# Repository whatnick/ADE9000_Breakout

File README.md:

# ADE9000 Breakout Board

Breadboard-compatible breakout for the Analog Devices [ADE9000](https://www.analog.com/en/products/ade9000.html) — a high-performance, multiphase energy and power quality monitoring IC.

The board follows the **test circuit from Figure 55 of the ADE9000 datasheet** (Rev. B, p. 28): all onboard passives (decoupling, RC anti-aliasing filters, crystal load caps, reset RC) are populated, power plus the analog channels are broken out to 0.1" headers, and the remaining digital signals are exposed on test pads to keep the board compact.

## 3D renders

These views are rendered from the populated KiCad assembly using the
project-local STEP models.

| Top isometric | Bottom isometric |
|---------------|------------------|
|  |  |

---

## Features

- **ADE9000** in 40-lead LFCSP (CP-40-7) package
- 3.3 V single-supply operation
- Onboard **24.576 MHz crystal** with 16 pF load caps (CLKIN/CLKOUT)
- Onboard **RC anti-aliasing filters** on all 7 analog input pairs (1 kΩ + 22 nF)
- Onboard **reset RC** (10 kΩ pull-up + 1 µF)
- Onboard **decoupling** on VDD, AVDDOUT, DVDDOUT, and REF per datasheet
- **CF2 activity LED** with 1 kΩ current-limit resistor
- **Power plus analog inputs** broken out to 0.1" headers
- **SPI, CF, IRQ, CLK, and RESET** exposed on test pads
- ATM90E36-style three-pad solder bridges for manual PM0/PM1 mode selection

---

## Pin Headers

### J1 — Power

| Pin | Signal | ADE9000 Pin | Description |
|-----|--------|-------------|-------------|
| 1 | 3.3V | — | Power in |
| 2 | GND | — | Ground |

### J2 — Current Inputs (left side, top)

| Pin | Signal | ADE9000 Pin | Description |
|-----|--------|-------------|-------------|
| 1 | IAP | 7 | Phase A current, positive |
| 2 | IAN | 8 | Phase A current, negative |
| 3 | IBP | 9 | Phase B current, positive |
| 4 | IBN | 10 | Phase B current, negative |
| 5 | ICP | 11 | Phase C current, positive |
| 6 | ICN | 12 | Phase C current, negative |
| 7 | INP | 13 | Neutral current, positive |
| 8 | INN | 14 | Neutral current, negative |

> Each input pair has a 1 kΩ series resistor and 22 nF cap to GND already fitted on board. Max differential input ±1 V / PGA gain.

### J3 — Voltage Inputs (left side, bottom)

| Pin | Signal | ADE9000 Pin | Description |
|-----|--------|-------------|-------------|
| 1 | VAP | 20 | Phase A voltage, positive |
| 2 | VAN | 19 | Phase A voltage, negative |
| 3 | VBP | 22 | Phase B voltage, positive |
| 4 | VBN | 21 | Phase B voltage, negative |
| 5 | VCP | 24 | Phase C voltage, positive |
| 6 | VCN | 23 | Phase C voltage, negative |

> Each input pair has the same 1 kΩ + 22 nF RC filter as the current inputs.

### Test Pads — Digital I/O

| Pad | Signal | ADE9000 Pin | Description |
|-----|--------|-------------|-------------|
| TP1 | SS | 40 | SPI slave select (active low) |
| TP2 | MOSI | 39 | SPI data in |
| TP3 | MISO | 38 | SPI data out |
| TP4 | SCLK | 37 | SPI clock (up to 20 MHz) |
| TP5 | IRQ0 | 31 | Interrupt output 0 (active low) |
| TP6 | IRQ1 | 32 | Interrupt output 1 (active low) |
| TP7 | CF1 | 33 | Calibration frequency output 1 |
| TP8 | CF2 | 34 | Calibration frequency output 2 / LED drive |
| TP9 | CF3_ZX | 35 | Zero-cross / CF3 output |
| TP10 | CF4_DREADY | 36 | Data-ready / event / CF4 output |
| TP11 | RESET | 6 | Reset (active low, RC-held high) |

---

## Power

- Supply **3.3 V** into the J1 3.3V pin (or the dedicated 3V3 pad).
- Current draw: ~15–17 mA in normal mode (PSM0).
- Onboard decoupling (per datasheet §Test Circuit):
  - **VDD** (pin 27): 10 µF + 0.1 µF ceramic to GND
  - **AVDDOUT** (pin 25): 4.7 µF + 0.1 µF ceramic to GND — **do not drive externally**
  - **DVDDOUT** (pin 3): 4.7 µF + 0.1 µF ceramic to GND — **do not drive externally**
  - **REF** (pin 16): 4.7 µF + 0.1 µF ceramic to REFGND (internal 1.25 V reference)

### PM0/PM1 mode bridges

`JP1` controls PM0 and `JP2` controls PM1. Each open three-pad jumper is marked
`1 PMx 0`: bridge the center pad to `1` for `+3V3`, or to `0` for `GND`.

| JP2 / PM1 | JP1 / PM0 | Selection |
|------------|-----------|-----------|
| 0 | 0 | Normal operation |
| 0 | 1 | PM1:PM0 = `01` |
| 1 | 0 | PM1:PM0 = `10` |
| 1 | 1 | PM1:PM0 = `11` |

Bridge exactly one side of each jumper before powering the board. Never bridge
both sides, and do not leave a mode pin floating. Production boards intended
for normal operation should have the `0` side bridged on both JP1 and JP2.

---

## Clock

A 24.576 MHz crystal is fitted between CLKIN (pin 29) and CLKOUT (pin 30) with 16 pF load capacitors to GND. This matches the ADE9000's required ±30 ppm clock.

To use an external clock instead, remove the crystal, leave the load caps unpopulated, and drive CLKIN directly (3.3 V logic, 24.330–24.822 MHz, 45:55–55:45 duty cycle).

---

## SPI Interface

The ADE9000 uses **SPI mode 0** (CPOL=0, CPHA=0), MSB first, up to **20 MHz**.

| Signal | Direction (from MCU) | Notes |
|--------|---------------------|-------|
| SCLK | Output | Max 20 MHz |
| MOSI | Output | 16-bit or 32-bit transfers |
| MISO | Input | |
| SS | Output | Assert low before each transfer |

All SPI pins are 3.3 V logic. Use a level shifter if connecting to a 5 V MCU.

---

## Analog Input Signal Conditioning

The onboard RC filter on each analog input pin:

```
Signal ──[ 1 kΩ ]──┬── IxP / VxP (ADE9000 pin)
                   │
                 [22 nF]
                   │
                  GND
```

This provides a first-order anti-aliasing LPF with fc ≈ 7.2 kHz, matching the ADC's −3 dB bandwidth. For CT or Rogowski coil inputs, drive the differential pair through an additional burden resistor or signal conditioning stage before these onboard filters.

---

## BOM Summary

Source purchasing fields live on the schematic symbols as `Manufacturer`, `MPN`, `DigiKey`, `Mouser`, and `Description` properties. Regenerate the grouped purchasing BOM with:

```powershell
& "C:\Program Files\KiCad\10.0\bin\python.exe" .\scripts\apply_bom_fields.py
& "C:\Program Files\KiCad\10.0\bin\python.exe" .\scripts\export_bom.py --html .\bom\ADE9000_Breakout_BOM.html
```

Generated outputs are available as [`bom/ADE9000_Breakout_BOM.csv`](bom/ADE9000_Breakout_BOM.csv), [`bom/ADE9000_Breakout_BOM.xlsx`](bom/ADE9000_Breakout_BOM.xlsx), and [`bom/ADE9000_Breakout_BOM.html`](bom/ADE9000_Breakout_BOM.html). The DigiKey and Mouser fields use distributor search URLs for the selected manufacturer MPNs so stock and packaging can be checked at order time.

| Ref | Value | Package | Notes |
|-----|-------|---------|-------|
| U1 | ADE9000 | CP-40-7 LFCSP | Main IC |
| Y1 | 24.576 MHz | 3225 (3.2×2.5 mm) | ±30 ppm |
| C_CLKIN, C_CLKOUT | 16 pF | 0402 | Crystal load caps |
| C_VDD1 | 10 µF | 0805 | VDD bulk decoupling |
| C_VDD2, C_AVDD2, C_DVDD2, C_REF2 | 0.1 µF | 0402 | HF decoupling |
| C_AVDD1, C_DVDD1, C_REF1 | 4.7 µF | 0805 | LF decoupling |
| C_RST | 1 µF | 0402 | Reset RC |
| C_PM | 1 µF | 0402 | PM0 bypass |
| R_RST | 10 kΩ | 0402 | Reset pull-up |
| R_IAP…R_VCN (×14) | 1 kΩ | 0402 | Anti-aliasing series R |
| C_IAP…C_VCN (×7) | 22 nF | 0402 | Anti-aliasing cap (differential) |
| R_LED | 1 kΩ | 0402 | CF2 LED current limit |
| D_LED | Green LED | 0402 | CF2 activity indicator |

---

## Schematic

The KiCad schematic (`ADE9000_Breakout.kicad_sch`) implements Figure 55 of the datasheet with compact breakout constraints: only power and analog channels go to headers, while digital signals stay on test pads. Reference images and the datasheet are in [`docs/`](docs/).

---

## 3D CAD

Project-local STEP models for all populated ADE9000 board parts are stored in [`models/step/`](models/step/). The PCB references these files through `${KIPRJMOD}` so the 3D view and CAD export do not depend on a particular KiCad library installation.

The digital/debug header `J1` uses SparkFun's staggered `1x16_Locking` friction-fit footprint, vendored at [`footprints/SparkFun-Connector.pretty/1x16_Locking.kicad_mod`](footprints/SparkFun-Connector.pretty/1x16_Locking.kicad_mod) from `sparkfun/SparkFun-KiCad-Libraries` commit `14865e2`. It keeps the 2.54 mm header pitch but alternates pad positions by 0.127 mm so a standard breakaway male header can lock into the board without solder during bench use. The SparkFun library is licensed CC BY 4.0; attribution: SparkFun Electronics.

The stereo CT jacks use a black AP214-colored STEP model at [`models/step/Jack_3.5mm_CUI_SJ-3523-SMT_Horizontal.step`](models/step/Jack_3.5mm_CUI_SJ-3523-SMT_Horizontal.step), generated from the manufacturer `SJ-3523-SMT-TR` CAD ZIP in [`models/step/SJ_3523_SMT_TR.zip`](models/step/SJ_3523_SMT_TR.zip) with [`scripts/create_sj3523_smt_step.py`](scripts/create_sj3523_smt_step.py). The script bakes the DigiKey/Same Sky CAD into the KiCad footprint frame with the front barrel on the footprint's board-edge side, without adding artificial pad overlays. Do not substitute the through-hole `SJ1-3523N` model for this SMT footprint.

The voltage screw-terminal footprints use KiCad's 1x02 3.50 mm horizontal Phoenix STEP model as the closest installed mechanical equivalent for the 4Ucon footprint, with model-only offset `(-1.75, -0.05, 0)` to align the substitute body to the 4Ucon footprint outline.

A full board assembly STEP export is available at [`exports/step/ADE9000_Breakout.step`](exports/step/ADE9000_Breakout.step). Regenerate it with:

```powershell
& "C:\Program Files\KiCad\10.0\bin\kicad-cli.exe" pcb export step --force --subst-models --output "exports\step\ADE9000_Breakout.step" "ADE9000_Breakout.kicad_pcb"
```

---

## Resources

| Document | Path |
|----------|------|
| ADE9000 Datasheet (Rev. B) | [`docs/ADE9000.pdf`](docs/ADE9000.pdf) |
| Test Circuit Reference | [`docs/images/test_ade9000.png`](docs/images/test_ade9000.png) |
| ADE9000 Product Page | https://www.analog.com/en/products/ade9000.html |
| ADE9000 Technical Reference Manual (UG-1098) | https://www.analog.com/media/en/technical-documentation/user-guides/ADE9000-UG-1098.pdf |
| Arduino Shield Eval (UG-1170) | https://www.analog.com/media/en/technical-documentation/user-guides/ev-ade9000shieldz-ug-1170.pdf |
| no-OS Driver | https://github.com/analogdevicesinc/no-OS/tree/main/drivers/meter/ade9000 |

---

## License

This hardware design is released under the [TAPR Open Hardware License v1.0](LICENSE). The PCB artwork includes a `TAPR OHL` notice on the back silkscreen.

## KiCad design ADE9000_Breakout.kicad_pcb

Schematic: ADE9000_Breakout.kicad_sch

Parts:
C1: 10uF; C_0805_2012Metric; MPN CL21A106KPFNNNE
C2, C4, C6, C8: 100nF; C_0603_1608Metric; MPN CC0603KPX7R0BB104
C3, C5, C7: 4.7uF; C_0805_2012Metric; MPN CL21A475KPFNNNE
C9, C10: 16pF; C_0603_1608Metric; MPN GRM1885C1H160JA01D
C11: 1uF; C_0603_1608Metric; MPN GRM188R61A105KA61D
C12, C13, C14, C15, C16, C17, C18, C19, C20, C21, C22, C23, C24, C25: 22nF; C_0603_1608Metric; MPN GRM188R71H223KA01D
CTA1: CT stereo jack; Jack_3.5mm_CUI_SJ-3523-SMT_Horizontal; MPN SJ-3523-SMT-TR
CTB1: CT stereo jack; Jack_3.5mm_CUI_SJ-3523-SMT_Horizontal; MPN SJ-3523-SMT-TR
CTC1: CT stereo jack; Jack_3.5mm_CUI_SJ-3523-SMT_Horizontal; MPN SJ-3523-SMT-TR
CTN1: CT stereo jack; Jack_3.5mm_CUI_SJ-3523-SMT_Horizontal; MPN SJ-3523-SMT-TR
D1: GREEN_LED; LED_0603_1608Metric; MPN LTST-C191KGKT
J1: Digital breadboard; 1x16_Locking; MPN PREC016SAAN-RC
J2, J3, J4: Voltage terminal; TerminalBlock_4Ucon_1x02_P3.50mm_Horizontal_ADE9000; MPN 1984617
JP1: PM0 mode; ModeBridge_3Pad
JP2: PM1 mode; ModeBridge_3Pad
R1: 10k; R_0603_1608Metric; MPN RC0603FR-0710KL
R2, R3, R4, R5, R6, R7, R8, R9, R10, R11, R12, R13, R14, R15, R16: 1k; R_0603_1608Metric; MPN RC0603FR-071KL
R17, R18, R19, R20: 2.4R; R_0603_1608Metric; MPN RC0603FR-072R4L
R21, R22, R23, R24, R25, R26: 100k; R_0603_1608Metric; MPN RC0603FR-07100KL
R27, R28, R29, R30, R31, R32: 2.49k; R_0603_1608Metric; MPN RC0603FR-072K49L
U1: ADE9000; QFN-40-1EP_6x6mm_P0.5mm_EP4.27x4.27mm; MPN ADE9000ACPZ
Y1: 24.576MHz; Crystal_SMD_3225-4Pin_3.2x2.5mm; MPN ECS-245.7-12-33Q-JES-TR

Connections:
+3V3: C1.2, C2.2, J1.1, JP1.1 (A), JP2.1 (A), R1.2, U1.1 (PULL_HIGH), U1.27 (VDD)
AVDDOUT: C3.2, C4.2, U1.25 (AVDDOUT)
CF1: J1.9, U1.33 (CF1)
CF2: J1.10, R16.2, U1.34 (CF2)
CF2_LED: D1.2 (A), R16.1
CF3_ZX: J1.11, U1.35 (CF3/ZX)
CF4_DREADY: J1.12, U1.36 (CF4/~DREADY)
CLKIN: C9.2, J1.14, U1.29 (CLKIN), Y1.1
CLKOUT: C10.2, J1.15, U1.30 (CLKOUT), Y1.2
DVDDOUT: C5.2, C6.2, U1.3 (DVDDOUT)
GND: C1.1, C2.1, C3.1, C4.1, C5.1, C6.1, C7.1, C8.1, C9.1, C10.1, C11.1, C12.2, C13.2, C14.2, C15.2, C16.2, C17.2, C18.2, C19.2, C20.2, C21.2, C22.2, C23.2, C24.2, C25.2, CTA1.R, CTB1.R, CTC1.R, CTN1.R, D1.1 (K), J1.2, J1.16, JP1.3 (B), JP2.3 (B), R27.2, R28.2, R29.2, R30.2, R31.2, R32.2, U1.2 (DGND), U1.15 (REFGND), U1.26 (AGND), U1.28 (GND), U1.EP (EPAD)
IAN: C13.1, R3.2, U1.8 (IAN)
IAN_J: CTA1.S, R3.1, R17.2
IAP: C12.1, R2.2, U1.7 (IAP)
IAP_J: CTA1.T, R2.1, R17.1
IBN: C15.1, R5.2, U1.10 (IBN)
IBN_J: CTB1.S, R5.1, R18.2
IBP: C14.1, R4.2, U1.9 (IBP)
IBP_J: CTB1.T, R4.1, R18.1
ICN: C17.1, R7.2, U1.12 (ICN)
ICN_J: CTC1.S, R7.1, R19.2
ICP: C16.1, R6.2, U1.11 (ICP)
ICP_J: CTC1.T, R6.1, R19.1
INN: C19.1, R9.2, U1.14 (INN)
INN_J: CTN1.S, R9.1, R20.2
INP: C18.1, R8.2, U1.13 (INP)
INP_J: CTN1.T, R8.1, R20.1
IRQ0: J1.7, U1.31 (~IRQ0)
IRQ1: J1.8, U1.32 (~IRQ1)
MISO: J1.5, U1.38 (MISO)
MOSI: J1.4, U1.39 (MOSI)
PM0: JP1.2 (C), U1.4 (PM0)
PM1: JP2.2 (C), U1.5 (PM1)
REF: C7.2, C8.2, U1.16 (REF)
RESET: C11.2, J1.13, R1.1, U1.6 (~RESET)
SCLK: J1.6, U1.37 (SCLK)
SS: J1.3, U1.40 (~SS)
VAN: C20.1, R10.2, U1.19 (VAN)
VAN_DIV: R10.1, R22.2, R28.1
VAN_J: J2.2, R22.1
VAP: C21.1, R11.2, U1.20 (VAP)
VAP_DIV: R11.1, R21.2, R27.1
VAP_J: J2.1, R21.1
VBN: C22.1, R12.2, U1.21 (VBN)
VBN_DIV: R12.1, R24.2, R30.1
VBN_J: J3.2, R24.1
VBP: C23.1, R13.2, U1.22 (VBP)
VBP_DIV: R13.1, R23.2, R29.1
VBP_J: J3.1, R23.1
VCN: C24.1, R14.2, U1.23 (VCN)
VCN_DIV: R14.1, R26.2, R32.1
VCN_J: J4.2, R26.1
VCP: C25.1, R15.2, U1.24 (VCP)
VCP_DIV: R15.1, R25.2, R31.1
VCP_J: J4.1, R25.1

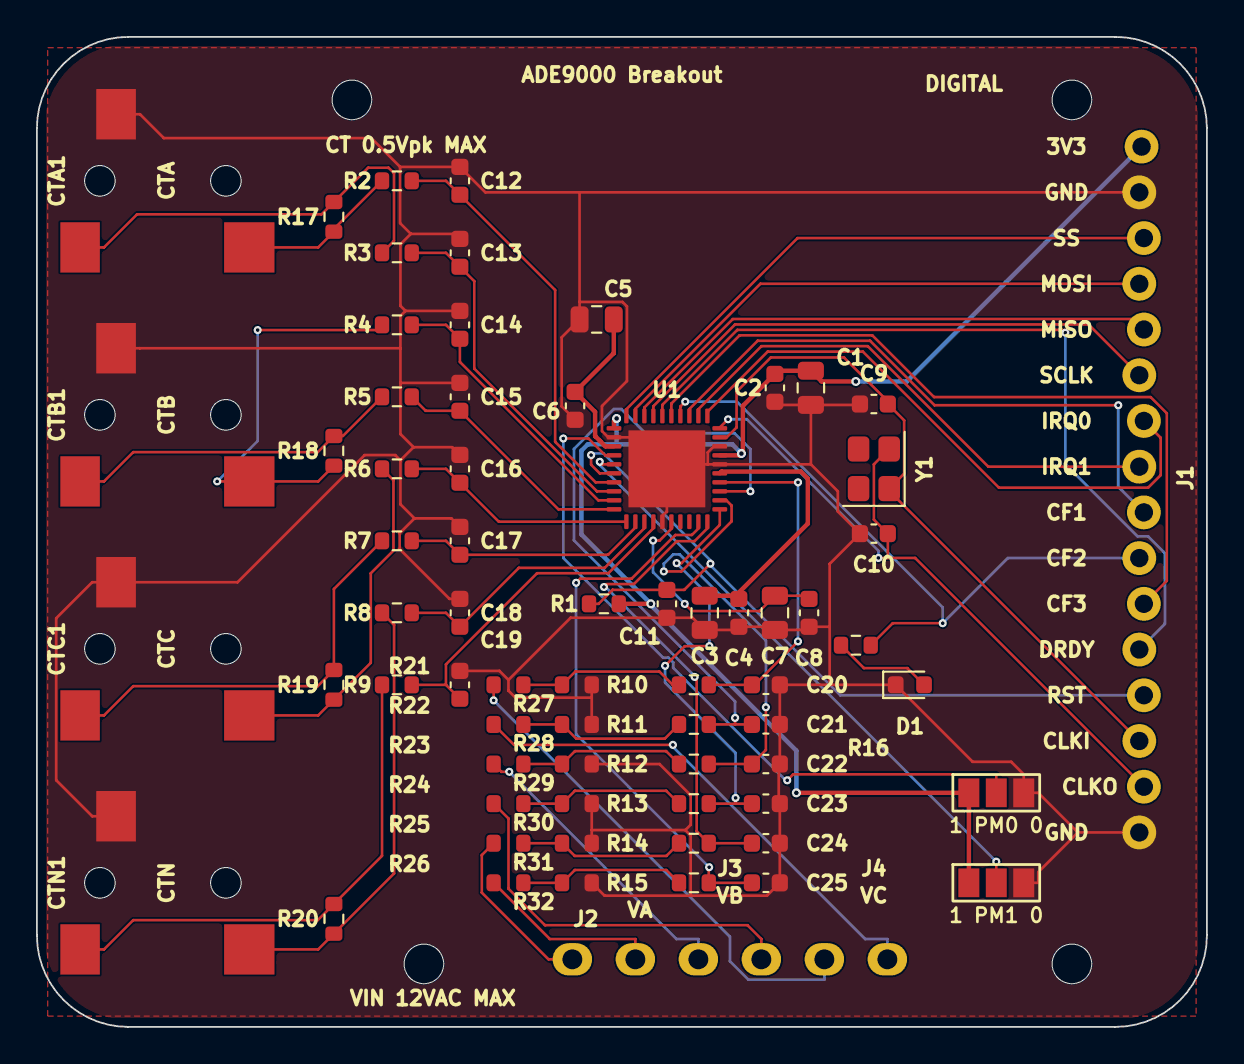
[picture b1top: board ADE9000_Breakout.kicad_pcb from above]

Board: 2 copper layers, 65.0 x 55.0 mm, 75 parts (1 on the bottom side), 55 nets.

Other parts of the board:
H1, H2, H3, H4: MountingHole_2.2mm_M2
LOGO1: OSHW-LOGOM; OSHW-Logo2_7.3x6mm_SilkScreen

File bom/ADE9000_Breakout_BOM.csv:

Line,Quantity,References,Value,Footprint,Manufacturer,MPN,DigiKey,Mouser,Description
1,1,C1,10uF,Capacitor_SMD:C_0805_2012Metric,Samsung Electro-Mechanics,CL21A106KPFNNNE,https://www.digikey.com/en/products/result?keywords=CL21A106KPFNNNE,https://www.mouser.com/c/?q=CL21A106KPFNNNE,10 uF 10 V X5R 0805 ceramic capacitor
2,4,"C2, C4, C6, C8",100nF,Capacitor_SMD:C_0603_1608Metric,YAGEO,CC0603KPX7R0BB104,https://www.digikey.com.au/en/products/detail/yageo/CC0603KP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,https://www.mouser.com/c/?q=CC0603KPX7R0BB104,100 nF 100 V 10% X7R 0603 ceramic capacitor
3,3,"C3, C5, C7",4.7uF,Capacitor_SMD:C_0805_2012Metric,Samsung Electro-Mechanics,CL21A475KPFNNNE,https://www.digikey.com/en/products/result?keywords=CL21A475KPFNNNE,https://www.mouser.com/c/?q=CL21A475KPFNNNE,4.7 uF 10 V X5R 0805 ceramic capacitor
4,2,"C9, C10",16pF,Capacitor_SMD:C_0603_1608Metric,Murata,GRM1885C1H160JA01D,https://www.digikey.com/en/products/result?keywords=GRM1885C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,https://www.mouser.com/c/?q=GRM1885C1H160JA01D,16 pF 50 V C0G/NP0 0603 ceramic capacitor
5,1,C11,1uF,Capacitor_SMD:C_0603_1608Metric,Murata,GRM188R61A105KA61D,https://www.digikey.com/en/products/result?keywords=GRM188R6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,https://www.mouser.com/c/?q=GRM188R61A105KA61D,1 uF 10 V X5R 0603 ceramic capacitor
6,14,"C12, C13, C14, C15, C16, C17, C18, C19, C20, C21, C22, C23, C24, C25",22nF,Capacitor_SMD:C_0603_1608Metric,Murata,GRM188R71H223KA01D,https://www.digikey.com/en/products/result?keywords=GRM188R7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,https://www.mouser.com/c/?q=GRM188R71H223KA01D,22 nF 50 V X7R 0603 ceramic capacitor
7,4,"CTA1, CTB1, CTC1, CTN1",CT stereo jack,Connector_Audio:Jack_3.5mm_CUI_SJ-3523-SMT_Horizontal,Same Sky,SJ-3523-SMT-TR,https://www.digikey.com/en/products/result?keywords=SJ-3523-SMT-TR,https://www.mouser.com/c/?q=SJ-3523-SMT-TR,3.5 mm stereo SMT audio jack for current-transformer inputs
8,1,D1,GREEN_LED,LED_SMD:LED_0603_1608Metric,Lite-On,LTST-C191KGKT,https://www.digikey.com/en/products/result?keywords=LTST-C191KGKT,https://www.mouser.com/c/?q=LTST-C191KGKT,Green 0603 SMD LED
9,1,J1,Digital breadboard,SparkFun-Connector:1x16_Locking,Sullins Connector Solutions,PREC016SAAN-RC,https://www.digikey.com/en/products/result?keywords=PREC016SAAN-RC,https://www.mouser.com/c/?q=PREC016SAAN-RC,1x16 2.54 mm vertical breakaway male header for SparkFun locking footprint
10,3,"J2, J3, J4",Voltage terminal,ADE9000-Local:TerminalBlock_4Ucon_1x02_P3.50mm_Horizontal_ADE9000,Phoenix Contact,1984617,https://www.digikey.com/en/products/result?keywords=1984617,https://www.mouser.com/c/?q=1984617,2-position 3.5 mm horizontal screw terminal block
11,1,R1,10k,Resistor_SMD:R_0603_1608Metric,YAGEO,RC0603FR-0710KL,https://www.digikey.com/en/products/result?keywords=RC0603FR-0710KL,https://www.mouser.com/c/?q=RC0603FR-0710KL,10 kOhm 1% 0603 thick-film resistor
12,15,"R2, R3, R4, R5, R6, R7, R8, R9, R10, R11, R12, R13, R14, R15, R16",1k,Resistor_SMD:R_0603_1608Metric,YAGEO,RC0603FR-071KL,https://www.digikey.com/en/products/result?keywords=RC0603FR-071KL,https://www.mouser.com/c/?q=RC0603FR-071KL,1 kOhm 1% 0603 thick-film resistor
13,4,"R17, R18, R19, R20",2.4R,Resistor_SMD:R_0603_1608Metric,YAGEO,RC0603FR-072R4L,https://www.digikey.com/en/products/result?keywords=RC0603FR-072R4L,https://www.mouser.com/c/?q=RC0603FR-072R4L,2.4 Ohm 1% 0603 thick-film burden resistor
14,6,"R21, R22, R23, R24, R25, R26",100k,Resistor_SMD:R_0603_1608Metric,YAGEO,RC0603FR-07100KL,https://www.digikey.com/en/products/result?keywords=RC0603FR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,https://www.mouser.com/c/?q=RC0603FR-07100KL,100 kOhm 1% 0603 voltage-divider high-side resistor
15,6,"R27, R28, R29, R30, R31, R32",2.49k,Resistor_SMD:R_0603_1608Metric,YAGEO,RC0603FR-072K49L,https://www.digikey.com/en/products/result?keywords=RC0603FR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,https://www.mouser.com/c/?q=RC0603FR-072K49L,2.49 kOhm 1% 0603 voltage-divider shunt resistor
16,1,U1,ADE9000,Package_DFN_QFN:QFN-40-1EP_6x6mm_P0.5mm_EP4.27x4.27mm,Analog Devices,ADE9000ACPZ,https://www.digikey.com/en/products/result?keywords=ADE9000ACPZ,https://www.mouser.com/c/?q=ADE9000ACPZ,"ADE9000 polyphase energy and power quality monitoring IC, CP-40-7 LFCSP"
17,1,Y1,24.576MHz,Crystal:Crystal_SMD_3225-4Pin_3.2x2.5mm,ECS Inc.,ECS-245.7-12-33Q-JES-TR,https://www.digikey.com/en/products/result?keywords=ECS-245.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,https://www.mouser.com/c/?q=ECS-245.7-12-33Q-JES-TR,24.576 MHz 3.2 x 2.5 mm SMD crystal

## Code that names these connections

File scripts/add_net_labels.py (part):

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Net strategy:
- J1 pin1 → +3V3 label
- J1 pin2 → GND label
- J2/J3 connector pins → IAP_J, IAN_J ... nets (left side of resistors)
- Resistors R2..R15 connect IAP_J → IAP through 1kΩ
- Caps C12..C25 connect node IAP etc → GND
- U1 analog pins get IAP, IAN... labels
- U1 digital pins get test pad labels
- Test pads TP1..TP11 get matching labels
- Power ties: PULL_HIGH→+3V3, PM0→GND, PM1→GND, DGND→GND, AGND→GND, REFGND→GND, EPAD→GND
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    # (net_name, x, y)
    ("+3V3",   U1_LX, 70.79),   # PULL_HIGH  (pin1)  → +3V3
    ("GND",    U1_LX, 73.33),   # DGND       (pin2)  → GND
    # DVDDOUT (pin3) gets its own node: DVDDOUT net (power output)
    ("GND",    U1_LX, 78.41),   # PM0        (pin4)  → GND (SPI mode)
    ("GND",    U1_LX, 80.95),   # PM1        (pin5)  → GND (normal mode)
    ("RESET",  U1_LX, 83.49),   # ~RESET~    (pin6)
    # Analog current inputs
    ("IAP",    U1_LX, 86.03),
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    r = label(net, x, y, angle=0)
    print(f"  {ok(r)} label '{net}' @ ({x}, {y:.2f})")

# DVDDOUT output node label
r = label("DVDDOUT", U1_LX, 75.87, angle=0)
print(f"  {ok(r)} label 'DVDDOUT' @ ({U1_LX}, 75.87)")

print()
print("--- U1 Right Pin Labels (power + SPI + CF) ---")
right_pin_labels = [
    # (net_name, x, y)
    ("AVDDOUT", U1_RX, 79.68),   # pin25
    ("GND",     U1_RX, 82.22),   # AGND (pin26) → GND
    ("+3V3",    U1_RX, 84.76),   # VDD  (pin27) → +3V3 in
    ("GND",     U1_RX, 87.30),   # GND  (pin28)
    ("CLKIN",   U1_RX, 89.84),   # CLKIN (pin29)
    ("CLKOUT",  U1_RX, 92.38),   # CLKOUT (pin30)
    ("IRQ0",    U1_RX, 94.92),   # ~IRQ0~ (pin31)
    ("IRQ1",    U1_RX, 97.46),   # ~IRQ1~ (pin32)
    ("CF1",     U1_RX, 100.00),  # CF1 (pin33)
    ("CF2",     U1_RX, 102.54),  # CF2 (pin34)
    ("CF3_ZX",  U1_RX, 105.08),  # CF3/ZX (pin35)
    ("CF4_DREADY", U1_RX, 107.62),  # CF4/DREADY (pin36)
    ("SCLK",    U1_RX, 110.16),  # SCLK (pin37)
    ("MISO",    U1_RX, 112.70),  # MISO (pin38)
    ("MOSI",    U1_RX, 115.24),  # MOSI (pin39)
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# ─── J2 CURRENT CONNECTOR ────────────────────────────────────────────────────
# Conn_01x08 at (35, 96.19) — pin ends at x=29.92
# Pin y-positions: pin1(bottom)=103.81, pin2=101.27, ..., pin8(top)=86.03
# Net assignment (bottom=pin1=INN, top=pin8=IAP):
print()
print("--- J2 Current Connector ---")
j2_pins = [
    (29.92, 103.81, "INN_J"),  # pin1
    (29.92, 101.27, "INP_J"),  # pin2
    (29.92,  98.73, "ICN_J"),  # pin3
    (29.92,  96.19, "ICP_J"),  # pin4
    (29.92,  93.65, "IBN_J"),  # pin5
    (29.92,  91.11, "IBP_J"),  # pin6
    (29.92,  88.57, "IAN_J"),  # pin7
    (29.92,  86.03, "IAP_J"),  # pin8
]
for x, y, net in j2_pins:
    r = label(net, x, y, angle=180)
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print()
print("--- J3 Voltage Connector ---")
j3_pins = [
    (29.92, 129.21, "VCP_J"),  # pin1
    (29.92, 126.67, "VCN_J"),  # pin2
    (29.92, 124.13, "VBP_J"),  # pin3
    (29.92, 121.59, "VBN_J"),  # pin4
    (29.92, 119.05, "VAP_J"),  # pin5
    (29.92, 116.51, "VAN_J"),  # pin6
]
for x, y, net in j3_pins:
    r = label(net, x, y, angle=180)
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# ─── POWER DECOUPLING CAPS C1–C8 ─────────────────────────────────────────────
# All caps: pin1 at (x, y+3.81), pin2 at (x, y-3.81)
# VDD decoupling (C1, C2) near VDD at (157/163, 83)
# pin1 → +3V3 or AVDDOUT/DVDDOUT/REF; pin2 → GND
print()
print("--- Decoupling Cap Labels ---")
decoup_caps = [
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# CLKIN net on left, CLKOUT on right
print()
print("--- Crystal Labels ---")
r = label("CLKIN",  153.19, 91, angle=180)
print(f"  {ok(r)} Y1 pin1 → CLKIN")
r = label("CLKOUT", 160.81, 91, angle=0)
print(f"  {ok(r)} Y1 pin2 → CLKOUT")

# C9 @ (163, 89): pin1 top = CLKIN, pin2 bottom = GND
# C10 @ (163, 93): pin1 top = CLKOUT, pin2 bottom = GND
r = label("CLKIN",  163, 89 + 3.81, angle=0)
r = label("GND",    163, 89 - 3.81, angle=0)
print(f"  {ok(r)} C9: CLKIN / GND")
r = label("CLKOUT", 163, 93 + 3.81, angle=0)
r = label("GND",    163, 93 - 3.81, angle=0)
print(f"  {ok(r)} C10: CLKOUT / GND")

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    print(f"  {ok(r)} TP '{net}' @ ({pin_x:.2f}, {y:.2f})")

# ─── LED / CF2 INDICATOR ─────────────────────────────────────────────────────
# R16 @ (157, 102): pin1 top=(157, 105.81)=+3V3, pin2 bot=(157, 98.19)=CF2_LED
# D1  @ (157, 106): pin1 top=(157, 109.81)=CF2_LED, pin2 bot=(157, 102.19)→GND
# Wait - Device:LED has anode at pin1 and cathode at pin2
# Typical LED circuit: +3V3 → R16 → anode (LED) → cathode → GND
# But CF2 is an output pulse from IC — connect as: CF2 → R16 → anode → cathode → GND
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print("--- CF2 LED indicator labels ---")
r = label("CF2",  157, 102 + 3.81, angle=0)
print(f"  {ok(r)} R16 pin1 → CF2")
r = label("CF2_LED", 157, 102 - 3.81, angle=0)
print(f"  {ok(r)} R16 pin2 → CF2_LED")
r = label("CF2_LED", 157, 106 + 3.81, angle=0)
print(f"  {ok(r)} D1 pin1 → CF2_LED")
r = label("GND",  157, 106 - 3.81, angle=0)
print(f"  {ok(r)} D1 pin2 → GND")

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
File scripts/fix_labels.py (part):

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
Root cause of issues discovered via PinLocator:
1. ADE9000 symbol has pins in REVERSED y-order from what was assumed.
   - pin24 (VCP) is at the TOP of U1's left side (y=70.79)
   - pin1 (PULL_HIGH) is at the BOTTOM (y=129.21)
   - Same for right side: EPAD at top (y=79.68), AVDDOUT at bottom (y=120.32)
2. KiCad symbol y-axis in schematic is INVERTED from symbol file y-axis.
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
# U1 LEFT SIDE (x=117.3, angle=0 — labels face right, stub on left)
# Pins verified by PinLocator. ADE9000 symbol has REVERSED pin order:
# physical pin 24 (VCP) at y=70.79 (TOP), physical pin 1 (PULL_HIGH) at y=129.21 (BOTTOM)
U1_LX = 117.3
U1_RX = 142.7

print("--- U1 Left Side (pins at x=117.3) ---")
# Format: (net_name, y_position, comment)
u1_left = [
    ("VCP",     70.79,  "pin24 VCP"),
    ("VCN",     73.33,  "pin23 VCN"),
    ("VBP",     75.87,  "pin22 VBP"),
    ("VBN",     78.41,  "pin21 VBN"),
    ("VAP",     80.95,  "pin20 VAP"),
    ("VAN",     83.49,  "pin19 VAN"),
    # pin18 NC at 86.03 → no_connect
    # pin17 NC at 88.57 → no_connect
    ("REF",     91.11,  "pin16 REF"),
    ("GND",     93.65,  "pin15 REFGND→GND"),
    ("INN",     96.19,  "pin14 INN"),
    ("INP",     98.73,  "pin13 INP"),
    ("ICN",     101.27, "pin12 ICN"),
    ("ICP",     103.81, "pin11 ICP"),
    ("IBN",     106.35, "pin10 IBN"),
    ("IBP",     108.89, "pin9 IBP"),
    ("IAN",     111.43, "pin8 IAN"),
    ("IAP",     113.97, "pin7 IAP"),
    ("RESET",   116.51, "pin6 ~RESET~"),
    ("GND",     119.05, "pin5 PM1→GND"),
    ("GND",     121.59, "pin4 PM0→GND"),
    ("DVDDOUT", 124.13, "pin3 DVDDOUT"),
    ("GND",     126.67, "pin2 DGND→GND"),
    ("+3V3",    129.21, "pin1 PULL_HIGH→+3V3"),
]
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    ("MOSI",         84.76,  "pin39 MOSI"),
    ("MISO",         87.30,  "pin38 MISO"),
    ("SCLK",         89.84,  "pin37 SCLK"),
    ("CF4_DREADY",   92.38,  "pin36 CF4/DREADY"),
    ("CF3_ZX",       94.92,  "pin35 CF3/ZX"),
    ("CF2",          97.46,  "pin34 CF2"),
    ("CF1",          100.00, "pin33 CF1"),
    ("IRQ1",         102.54, "pin32 ~IRQ1~"),
    ("IRQ0",         105.08, "pin31 ~IRQ0~"),
    ("CLKOUT",       107.62, "pin30 CLKOUT"),
    ("CLKIN",        110.16, "pin29 CLKIN"),
    ("GND",          112.70, "pin28 GND"),
    ("+3V3",         115.24, "pin27 VDD→+3V3"),
    ("GND",          117.78, "pin26 AGND→GND"),
    ("AVDDOUT",      120.32, "pin25 AVDDOUT"),
]
for net, y, comment in u1_right:
    r = lbl(net, U1_RX, y, angle=180)
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
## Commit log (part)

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2026-05-07 Initial AI Creation
2026-05-07 Make PCB and design skills
2026-05-07 Complete routing
2026-05-08 Some silk screen vagaries
2026-05-09 Reroute with JST connector for SPI
2026-05-09 Move decoupling closer
2026-05-11 Relayout using connectors for analog inputs
2026-05-16 Rerouted with Groundplanes and new skills
2026-05-16 Added License
2026-05-17 Add project-local 3D CAD assets
2026-05-17 Fix CT jack STEP orientation
2026-05-17 Remove CT jack pad overlays
2026-05-18 Align voltage terminal models
2026-05-18 Mirror manual terminal model alignment
2026-05-18 Clear silkscreen DRC warnings
2026-05-18 Use SparkFun locking digital header
2026-05-18 Add sourced BOM export flow
2026-05-18 Add reusable BOM sourcing skill
2026-05-18 Initial IBom
2026-05-18 Ibom restore
2026-05-18 Add 12 VAC voltage input support
2026-05-18 Move SMD parts to front side
2026-05-18 Use 0603 passives for hand assembly
2026-05-19 Add upscaling parts
